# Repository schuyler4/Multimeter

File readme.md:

<h2>Multimeter</h2>
<p>
This is my homebrew multimeter. It differs from standard multimeters in several
respects. 
</p>
<ol>
<li>Only the most used modes are actually included: VDC, Ohms, Capacitance</li>
<li>Powered by a USB cable, no changing batteries.</li> 
<li>Generally a different user interface because of 1 and 2.</li>
</ol>
<p align="center">
</img>
</p>
<h3>Calibration</h3>
<p>
Calibration is relative to my Fluke 101 Multimeter. I know that there
is probably some technical problems with this, as the Fluke 101 does
not have more digits than this meter, nor is it substantially more
 accurate in
voltage mode. However, I don't have a really nice bench top meter, so it 
will have to do. 
</p>
<h3>Specs</h3>
<ul>
<li>Input Resistance: 521kΩ </li>
<li>Range</li>
<ul>
<li>Voltage: +/-60V</li>
<li>Resistance Range 1: 30Ω - 1.2kΩ</li>
<li>Resistance Range 2: 1.2kΩ - 500kΩ</li>
<li>Capacitance: 50nF - 47uF </li>
</ul>
<li>
Relative Accuracy
<ul>
<li> Voltage: 0.5% </li> 
<li> Resistance: 10% </li>
<li> Capacitance: 5% </li>
</ul>
</ul>

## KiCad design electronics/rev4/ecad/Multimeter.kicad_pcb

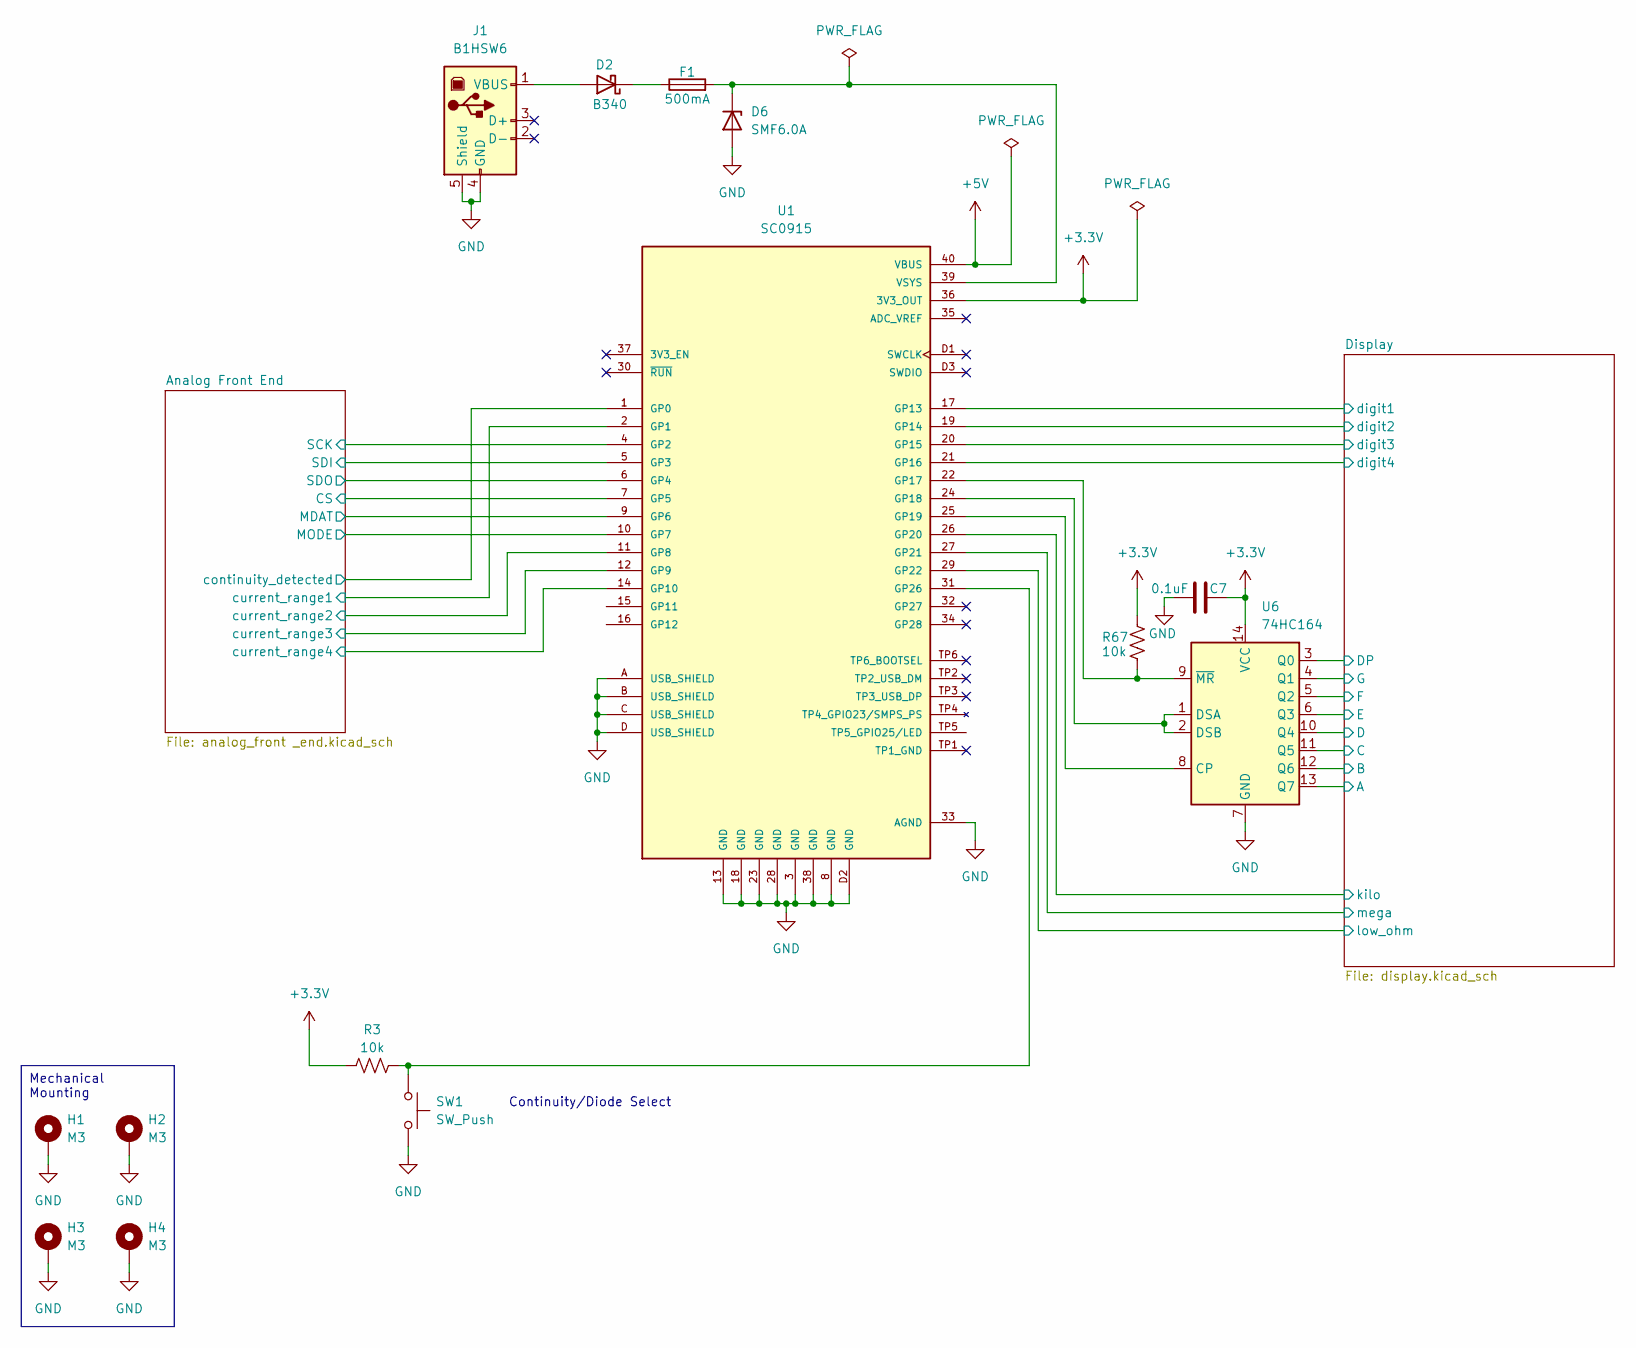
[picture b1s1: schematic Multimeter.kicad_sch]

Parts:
C7: 0.1uF
D2: B340; D_SMB; Part # B340LB-13-F; Digikey Part # B340LB-FDICT-ND
D6: SMF6.0A; D_SOD-123F; Part # SMF6.0A; Digikey Part # F5749CT-ND
F1: 500mA; Fuse_0805_2012Metric; Part # MFU0805FF00500P500; Digikey Part # 749-MFU0805FF00500P500CT-ND
H1, H2, H3, H4: M3; MountingHole_3.2mm_M3_Pad_Via
J1: B1HSW6; USB_B_OST_USB-B1HSxx_Horizontal; Part # USB-B1HSW6; Digikey Part # ED2982-ND
R3: 10k; R_0805_2012Metric; Part # RMCF0805FT10K0; Digikey Part # RMCF0805FT10K0CT-ND
R67: 10k
SW1: SW_Push; SW_PUSH_6mm; Part # TL1105YF160Q; Digikey Part # EG5455-ND
U1: SC0915; MODULE_SC0915; PARTREV 1.9; Digikey Part # 2648-SC0915CT-ND
U6: 74HC164

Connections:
+3.3V: C7.2, R3.1, R67.1, U1.36 (3V3_OUT), U6.14 (VCC); also elsewhere on the board
+5V: U1.40 (VBUS); also elsewhere on the board
/Analog Front End/CS: U1.7 (GP5); also elsewhere on the board
/Analog Front End/MDAT: U1.9 (GP6); also elsewhere on the board
/Analog Front End/MODE: U1.10 (GP7); also elsewhere on the board
/Analog Front End/SCK: U1.4 (GP2); also elsewhere on the board
/Analog Front End/SDI: U1.5 (GP3); also elsewhere on the board
/Analog Front End/SDO: U1.6 (GP4); also elsewhere on the board
/Analog Front End/continuity_detected: U1.1 (GP0); also elsewhere on the board
/Analog Front End/current_range1: U1.2 (GP1); also elsewhere on the board
/Analog Front End/current_range2: U1.11 (GP8); also elsewhere on the board
/Analog Front End/current_range3: U1.12 (GP9); also elsewhere on the board
/Analog Front End/current_range4: U1.14 (GP10); also elsewhere on the board
/Display/A: U1.34 (GP28); also elsewhere on the board
/Display/B: U1.32 (GP27); also elsewhere on the board
/Display/D: U1.29 (GP22); also elsewhere on the board
/Display/DP: U1.24 (GP18), U6.1 (DSA), U6.2 (DSB); also elsewhere on the board
/Display/E: U1.27 (GP21); also elsewhere on the board
/Display/F: U1.26 (GP20); also elsewhere on the board
/Display/G: U1.25 (GP19), U6.8 (CP); also elsewhere on the board
/Display/digit1: U1.17 (GP13); also elsewhere on the board
/Display/digit2: U1.19 (GP14); also elsewhere on the board
/Display/digit3: U1.20 (GP15); also elsewhere on the board
/Display/digit4: U1.21 (GP16); also elsewhere on the board
/Display/kilo: R67.2, U1.22 (GP17), U6.9 (~MR); also elsewhere on the board
/Display/low_ohm: U1.16 (GP12); also elsewhere on the board
/Display/mega: U1.15 (GP11); also elsewhere on the board
GND: C7.1, D6.2 (A), H1.1, H2.1, H3.1, H4.1, J1.4 (GND), J1.5 (Shield), SW1.2, U1.3 (GND), U1.8 (GND), U1.13 (GND), U1.18 (GND), U1.23 (GND), U1.28 (GND), U1.33 (AGND), U1.38 (GND), U1.A (USB_SHIELD), U1.B (USB_SHIELD), U1.C (USB_SHIELD), U1.D (USB_SHIELD), U1.D2 (GND), U6.7 (GND); also elsewhere on the board
unnamed: D2.2 (A), J1.1 (VBUS)
unnamed: D2.1 (K), F1.1
unnamed: D6.1 (K), F1.2, U1.39 (VSYS)

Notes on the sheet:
Mechanical Mounting
Continuity/Diode Select

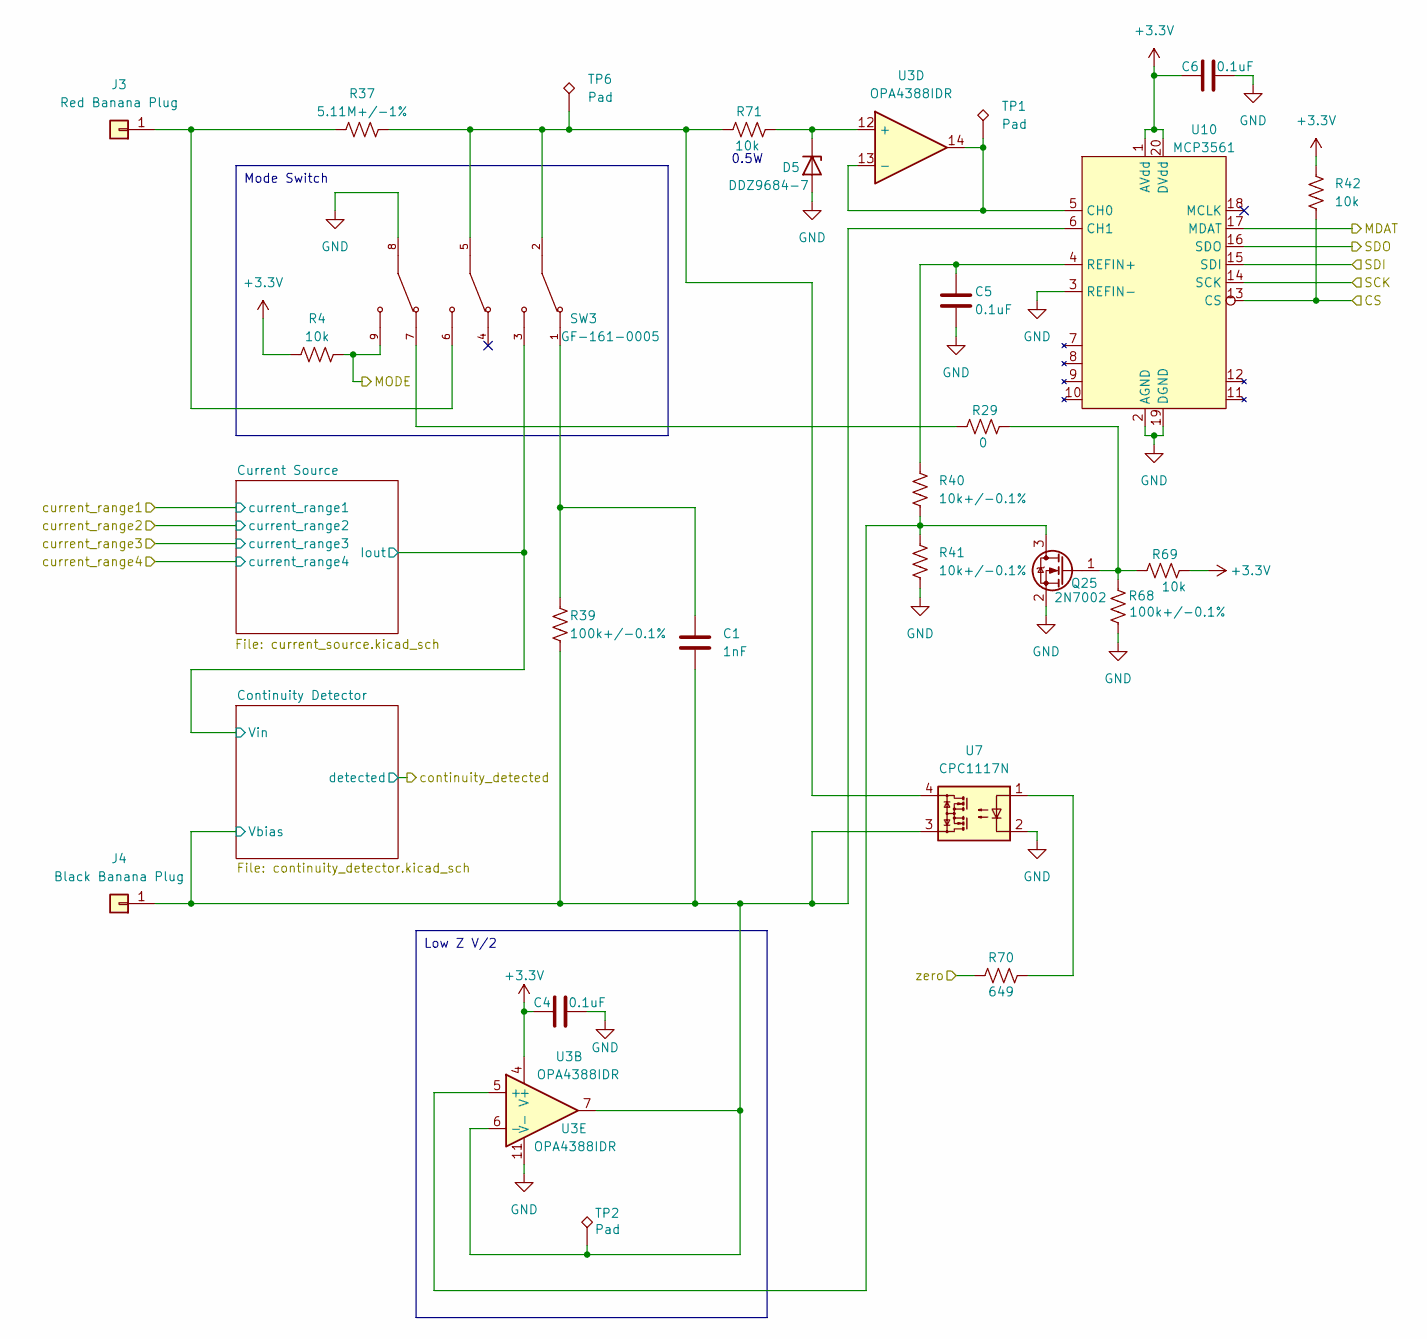
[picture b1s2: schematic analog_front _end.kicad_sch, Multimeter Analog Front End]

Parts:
C1: 1nF; C_0805_2012Metric; Part # CL21B104KBCNNNC; Digikey Part # 1276-1003-1-ND
C4, C5, C6: 0.1uF; C_0805_2012Metric; Part # CL21B104KBCNNNC; Digikey Part # 1276-1003-1-ND
D5: DDZ9684-7; D_SOD-123; Part # DDZ9684-7; Digikey Part # DDZ9684-7DICT-ND
J3: Red Banana Plug; KEYSTONE_575-4; Part # 575-8; Digikey Part # 36-575-8-ND
J4: Black Banana Plug; KEYSTONE_575-4; Part # 575-8; Digikey Part # 36-575-8-ND
Q25: 2N7002; SOT-23; Part # 2N7002; Digikey Part # 2N7002NCT-ND
R4, R42, R69: 10k; R_0805_2012Metric; Part # RMCF0805FT10K0; Digikey Part # RMCF0805FT10K0CT-ND
R29: 0; R_0805_2012Metric; Part # CRCW08050000Z0EA; Digikey Part # 541-0.0ACT-ND
R37: 5.11M+/-1%; R_0805_2012Metric; Part # CRCW08055M11FKEA; Digikey Part # 541-5.11MCCT-ND
R39, R68: 100k+/-0.1%; R_0805_2012Metric; Part # ERA-6AEB104V; Digikey Part # P100KDACT-ND
R40, R41: 10k+/-0.1%; R_0805_2012Metric; Part # ERA-6AEB103V; Digikey Part # P10KDACT-ND
R70: 649
R71: 10k
SW3: GF-161-0005; PARTREV 0; Digikey Part # CWI359-ND
TP1, TP2, TP6: Pad; TestPoint_THTPad_1.5x1.5mm_Drill0.7mm
U3: OPA4388IDR; SOIC-14_3.9x8.7mm_P1.27mm; Part # OPA4388IDR; Digikey Part # 296-53511-1-ND
U7: CPC1117N; SOP-4_3.8x4.1mm_P2.54mm
U10: MCP3561; SSOP-20_4.4x6.5mm_P0.65mm; Part # MCP3561RT-E/ST; Digikey Part # 150-MCP3561RT-E/STCT-ND

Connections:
+3.3V: C4.1, C6.1, R4.1, R42.1, R69.2, U3.4 (V+), U10.1 (AVdd), U10.20 (DVdd); also elsewhere on the board
/Analog Front End/CS: R42.2, U10.13 (CS); also elsewhere on the board
/Analog Front End/Continuity Detector/Vbias: C1.2, J4.1, R39.2, TP2.1, U3.6 (-), U3.7, U7.3, U10.6 (CH1); also elsewhere on the board
/Analog Front End/Current Source/Iout: SW3.3; also elsewhere on the board
/Analog Front End/MDAT: U10.17 (MDAT); also elsewhere on the board
/Analog Front End/MODE: R4.2, SW3.9; also elsewhere on the board
/Analog Front End/SCK: U10.14 (SCK); also elsewhere on the board
/Analog Front End/SDI: U10.15 (SDI); also elsewhere on the board
/Analog Front End/SDO: U10.16 (SDO); also elsewhere on the board
GND: C4.2, C5.2, C6.2, D5.2 (A), Q25.2 (S), R41.2, R68.1, SW3.8, U3.11 (V-), U7.2, U10.2 (AGND), U10.3 (REFIN-), U10.19 (DGND); also elsewhere on the board
unnamed: C1.1, R39.1, SW3.1
unnamed: Q25.3 (D), R40.2, R41.1, U3.5 (+)
unnamed: Q25.1 (G), R29.2, R68.2, R69.1
unnamed: R29.1, SW3.7
unnamed: R70.2, U7.1
unnamed: TP1.1, U3.13 (-), U3.14, U10.5 (CH0)
unnamed: C5.1, R40.1, U10.4 (REFIN+)

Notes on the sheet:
Low Z V/2
Mode Switch
0.5W

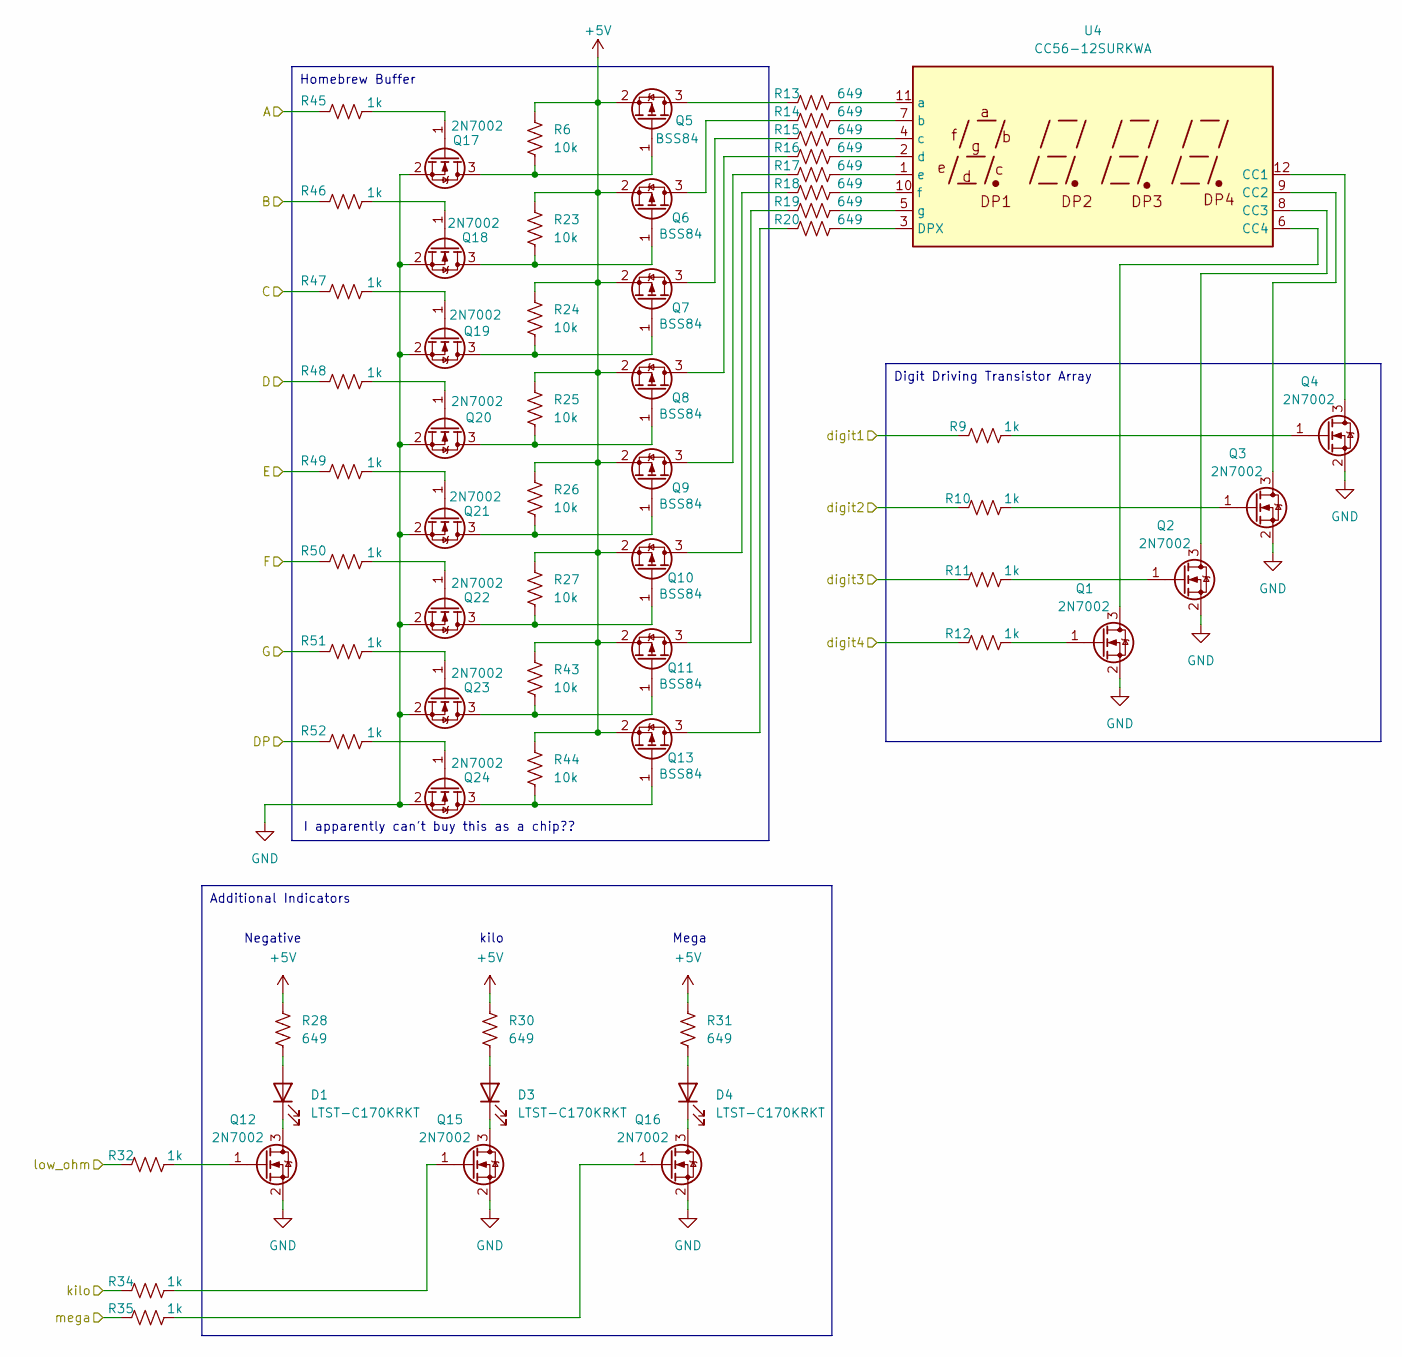
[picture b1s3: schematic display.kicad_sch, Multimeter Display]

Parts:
D1, D3, D4: LTST-C170KRKT; LED_0805_2012Metric; Part # LTST-C170KRKT; Digikey Part # 160-1415-1-ND
Q1, Q2, Q3, Q4, Q12, Q15, Q16, Q17, Q18, Q19, Q20, Q21, Q22, Q23, Q24: 2N7002; SOT-23; Part # 2N7002; Digikey Part # 2N7002NCT-ND
Q5, Q6, Q7, Q8, Q9, Q10, Q11, Q13: BSS84; SOT-23; Part # BSS84; Digikey Part # BSS84CT-ND
R6, R23, R24, R25, R26, R27, R43, R44: 10k; R_0805_2012Metric; Part # RMCF0805FT10K0; Digikey Part # RMCF0805FT10K0CT-ND
R9, R10, R11, R12, R32, R34, R35, R45, R46, R47, R48, R49, R50, R51, R52: 1k; R_0805_2012Metric; Part # RMCF0805FT1K00; Digikey Part # RMCF0805FT1K00CT-ND
R13, R14, R15, R16, R17, R18, R19, R20, R28, R30, R31: 649; R_0805_2012Metric; Part # RMCF0805FT649R; Digikey Part # RMCF0805FT649RCT-ND
U4: CC56-12SURKWA; CA56-12SURKWA; Part # CC56-12SURKWA; Digikey Part # 754-CC56-12SURKWA-ND

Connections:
+5V: Q5.2 (S), Q6.2 (S), Q7.2 (S), Q8.2 (S), Q9.2 (S), Q10.2 (S), Q11.2 (S), Q13.2 (S), R6.1, R23.1, R24.1, R25.1, R26.1, R27.1, R28.1, R30.1, R31.1, R43.1, R44.1; also elsewhere on the board
/Display/A: R45.1; also elsewhere on the board
/Display/B: R46.1; also elsewhere on the board
/Display/D: R48.1; also elsewhere on the board
/Display/DP: R52.1; also elsewhere on the board
/Display/E: R49.1; also elsewhere on the board
/Display/F: R50.1; also elsewhere on the board
/Display/G: R51.1; also elsewhere on the board
/Display/digit1: R9.1; also elsewhere on the board
/Display/digit2: R10.1; also elsewhere on the board
/Display/digit3: R11.1; also elsewhere on the board
/Display/digit4: R12.1; also elsewhere on the board
/Display/kilo: R34.1; also elsewhere on the board
/Display/low_ohm: R32.1; also elsewhere on the board
/Display/mega: R35.1; also elsewhere on the board
GND: Q1.2 (S), Q2.2 (S), Q3.2 (S), Q4.2 (S), Q12.2 (S), Q15.2 (S), Q16.2 (S), Q17.2 (S), Q18.2 (S), Q19.2 (S), Q20.2 (S), Q21.2 (S), Q22.2 (S), Q23.2 (S), Q24.2 (S); also elsewhere on the board
unnamed: D1.2 (A), R28.2
unnamed: D1.1 (K), Q12.3 (D)
unnamed: D3.2 (A), R30.2
unnamed: D3.1 (K), Q15.3 (D)
unnamed: D4.2 (A), R31.2
unnamed: D4.1 (K), Q16.3 (D)
unnamed: Q1.3 (D), U4.6 (CC4)
unnamed: Q1.1 (G), R12.2
unnamed: Q2.3 (D), U4.8 (CC3)
unnamed: Q2.1 (G), R11.2
unnamed: Q3.3 (D), U4.9 (CC2)
unnamed: Q3.1 (G), R10.2
unnamed: Q4.3 (D), U4.12 (CC1)
unnamed: Q4.1 (G), R9.2
unnamed: Q5.3 (D), R13.1
unnamed: Q6.3 (D), R14.1
unnamed: Q7.3 (D), R15.1
unnamed: Q8.3 (D), R16.1
unnamed: Q9.3 (D), R17.1
unnamed: Q10.3 (D), R18.1
unnamed: Q10.1 (G), Q22.3 (D), R27.2
unnamed: Q11.3 (D), R19.1
unnamed: Q11.1 (G), Q23.3 (D), R43.2
unnamed: Q12.1 (G), R32.2
unnamed: Q13.3 (D), R20.1
unnamed: Q13.1 (G), Q24.3 (D), R44.2
unnamed: Q15.1 (G), R34.2
unnamed: Q16.1 (G), R35.2
unnamed: Q5.1 (G), Q17.3 (D), R6.2
unnamed: Q17.1 (G), R45.2
unnamed: Q6.1 (G), Q18.3 (D), R23.2
unnamed: Q18.1 (G), R46.2
unnamed: Q7.1 (G), Q19.3 (D), R24.2
unnamed: Q19.1 (G), R47.2
unnamed: Q8.1 (G), Q20.3 (D), R25.2
unnamed: Q20.1 (G), R48.2
unnamed: Q9.1 (G), Q21.3 (D), R26.2
unnamed: Q21.1 (G), R49.2
unnamed: Q22.1 (G), R50.2
unnamed: Q23.1 (G), R51.2
unnamed: Q24.1 (G), R52.2
unnamed: R20.2, U4.3 (DPX)
unnamed: R13.2, U4.11 (a)
unnamed: R14.2, U4.7 (b)
unnamed: R15.2, U4.4 (c)
unnamed: R16.2, U4.2 (d)
unnamed: R17.2, U4.1 (e)
unnamed: R18.2, U4.10 (f)
unnamed: R19.2, U4.5 (g)

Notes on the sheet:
Digit Driving Transistor Array
Homebrew Buffer
Additional Indicators
kilo
I apparently can't buy this as a chip??
Mega
Negative

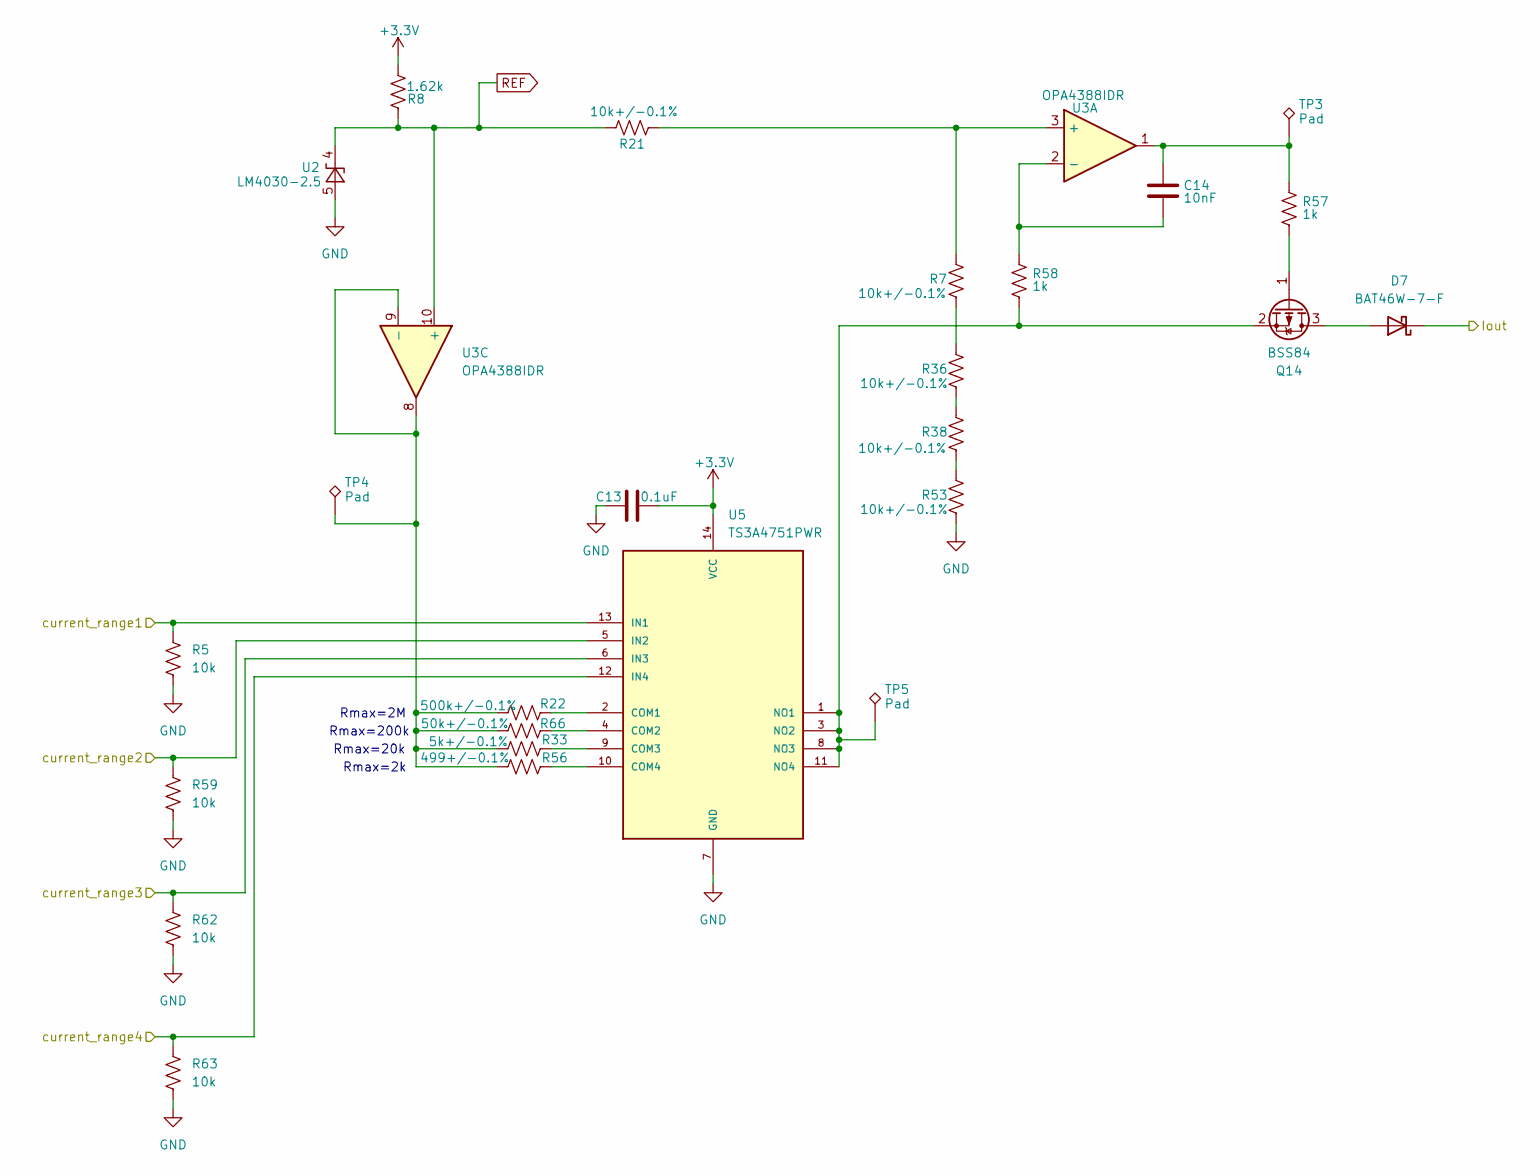
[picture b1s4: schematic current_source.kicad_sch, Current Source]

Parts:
C13: 0.1uF; C_0805_2012Metric; Part # CL21B104KBCNNNC; Digikey Part # 1276-1003-1-ND
C14: 10nF; C_0805_2012Metric; Part # C0805C103K5RACTU; Digikey Part # 399-C0805C103K5RACTUCT-ND
D7: BAT46W-7-F; D_SOD-123; Part # BAT46W-7-F; Digikey Part # BAT46W-7FDICT-ND
Q14: BSS84; SOT-23; Part # BSS84; Digikey Part # BSS84CT-ND
R5, R59, R62, R63: 10k; R_0805_2012Metric; Part # RMCF0805FT10K0; Digikey Part # RMCF0805FT10K0CT-ND
R7, R21, R36, R38, R53: 10k+/-0.1%; R_0805_2012Metric; Part # ERA-6AEB103V; Digikey Part # P10KDACT-ND
R8: 1.62k; R_0805_2012Metric; Part # RMCF0805FT1K62; Digikey Part # RMCF0805FT1K62CT-ND
R22: 500k+/-0.1%; R_0805_2012Metric; Part # RNCF0805BTE500K; Digikey Part # 738-RNCF0805BTE500KCT-ND
R33: 5k+/-0.1%; R_0805_2012Metric; Part # PNM0805E5001BST5; Digikey Part # PNM0805-5.0KBCT-ND
R56: 499+/-0.1%; R_0805_2012Metric; Part # ERA-6AEB4990V; Digikey Part # P499DACT-ND
R57, R58: 1k; R_0805_2012Metric; Part # RMCF0805FT1K00; Digikey Part # RMCF0805FT1K00CT-ND
R66: 50k+/-0.1%; R_0805_2012Metric; Part # MCU08050D5002BP100; Digikey Part # 749-MCU08050D5002BP100CT-ND
TP3, TP4, TP5: Pad; TestPoint_THTPad_1.5x1.5mm_Drill0.7mm
U2: LM4030-2.5; SOT-23-5; Part # LM4030CMF-2.5/NOPB; Digikey Part # LM4030CMF-2.5/NOPBCT-ND
U3: OPA4388IDR; SOIC-14_3.9x8.7mm_P1.27mm; Part # OPA4388IDR; Digikey Part # 296-53511-1-ND
U5: TS3A4751PWR; TSSOP-14_4.4x5mm_P0.65mm; PARTREV F; Digikey Part # 296-20700-1-ND

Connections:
+3.3V: C13.2, R8.1, U5.14 (VCC); also elsewhere on the board
/Analog Front End/Current Source/Iout: D7.1 (K); also elsewhere on the board
/Analog Front End/current_range1: R5.1, U5.13 (IN1); also elsewhere on the board
/Analog Front End/current_range2: R59.1, U5.5 (IN2); also elsewhere on the board
/Analog Front End/current_range3: R62.1, U5.6 (IN3); also elsewhere on the board
/Analog Front End/current_range4: R63.1, U5.12 (IN4); also elsewhere on the board
GND: C13.1, R5.2, R53.2, R59.2, R62.2, R63.2, U2.5 (A), U5.7 (GND); also elsewhere on the board
unnamed: C14.1, R57.1, TP3.1, U3.1
unnamed: D7.2 (A), Q14.3 (D)
unnamed: Q14.1 (G), R57.2
unnamed: Q14.2 (S), R58.2, TP5.1, U5.1 (NO1), U5.3 (NO2), U5.8 (NO3), U5.11 (NO4)
unnamed: R7.2, R36.1
unnamed: R36.2, R38.1
unnamed: R38.2, R53.1
unnamed: R7.1, R21.2, U3.3 (+)
unnamed: C14.2, R58.1, U3.2 (-)
unnamed: R22.1, R33.1, R56.1, R66.1, TP4.1, U3.8, U3.9 (-)
unnamed: R22.2, U5.2 (COM1)
unnamed: R66.2, U5.4 (COM2)
unnamed: R33.2, U5.9 (COM3)
unnamed: R56.2, U5.10 (COM4)
REF: R8.2, R21.1, U2.4 (K), U3.10 (+); also elsewhere on the board

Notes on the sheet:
Rmax=2M
Rmax=2k
Rmax=20k
Rmax=200k

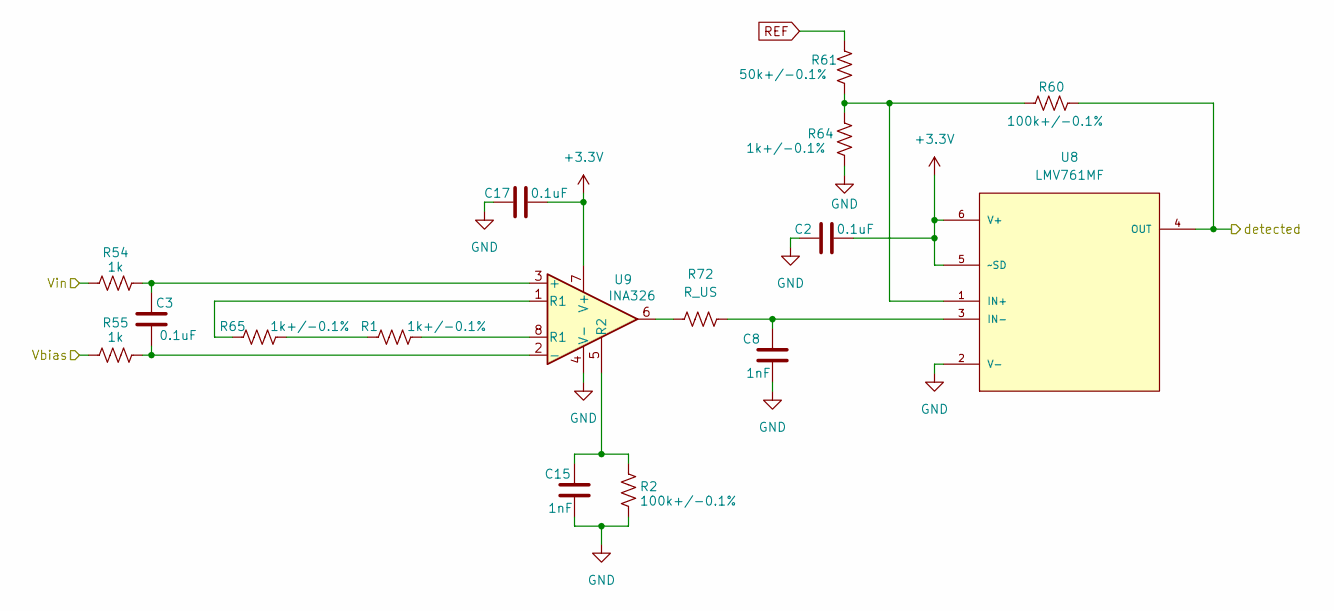
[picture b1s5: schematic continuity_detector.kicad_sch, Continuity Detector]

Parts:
C2, C3, C17: 0.1uF; C_0805_2012Metric; Part # CL21B104KBCNNNC; Digikey Part # 1276-1003-1-ND
C8, C15: 1nF; C_0805_2012Metric; Part # C0805C102J5GACTU; Digikey Part # 399-C0805C102J5GACTUCT-ND
R1, R64, R65: 1k+/-0.1%; R_0805_2012Metric; Part # CRCW08051K00FKEA; Digikey Part # 541-1.00KCCT-ND
R2, R60: 100k+/-0.1%; R_0805_2012Metric; Part # ERA-6AEB104V; Digikey Part # P100KDACT-ND
R54, R55: 1k; R_0805_2012Metric; Part # RMCF0805FT1K00; Digikey Part # RMCF0805FT1K00CT-ND
R61: 50k+/-0.1%; R_0805_2012Metric; Part # MCU08050D5002BP100; Digikey Part # 749-MCU08050D5002BP100CT-ND
R72: R_US
U8: LMV761MF; SOT-23-6; MPN LMV761MF; Digikey Part # LMV761MFCT-ND
U9: INA326; MSOP-8_3x3mm_P0.65mm; Part # INA326EA/2K5; Digikey Part # INA326EA/2K5CT-ND

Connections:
+3.3V: C2.2, C17.2, U8.5 (~SD), U8.6 (V+), U9.7 (V+); also elsewhere on the board
/Analog Front End/Continuity Detector/Vbias: R55.1; also elsewhere on the board
/Analog Front End/continuity_detected: R60.2, U8.4 (OUT); also elsewhere on the board
GND: C2.1, C8.2, C15.2, C17.1, R2.2, R64.2, U8.2 (V-), U9.4 (V-); also elsewhere on the board
unnamed: R1.1, R65.2
unnamed: R1.2, U9.8 (R1)
unnamed: R65.1, U9.1 (R1)
unnamed: R60.1, R61.2, R64.1, U8.1 (IN+)
unnamed: C8.1, R72.1, R72.2, U8.3 (IN-), U9.6
unnamed: C3.1, R54.2, U9.3 (+)
unnamed: C3.2, R55.2, U9.2 (-)
unnamed: C15.1, R2.1, U9.5 (R2)
REF: R61.1; also elsewhere on the board

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
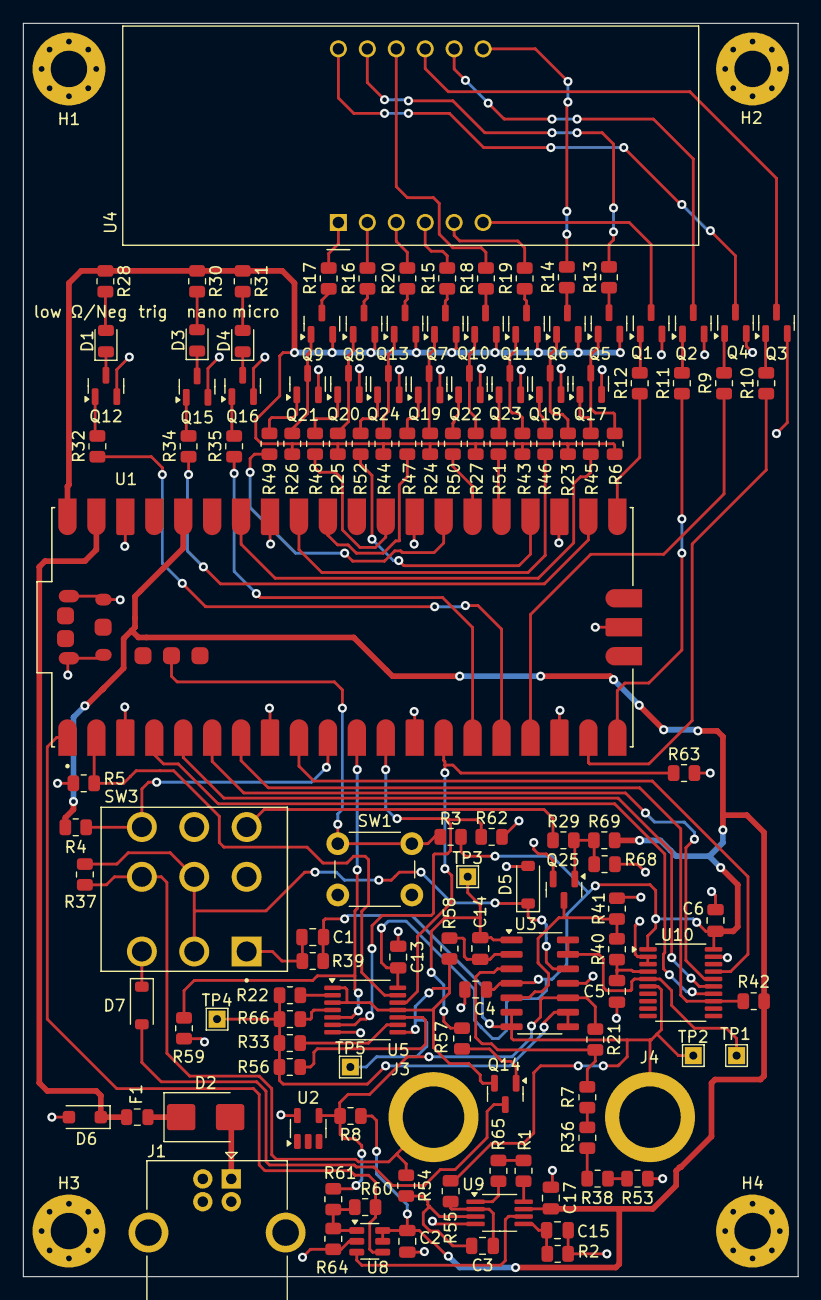
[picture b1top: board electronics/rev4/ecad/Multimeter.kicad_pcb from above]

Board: 2 copper layers, 68.0 x 110.0 mm, 133 parts (0 on the bottom side), 115 nets.

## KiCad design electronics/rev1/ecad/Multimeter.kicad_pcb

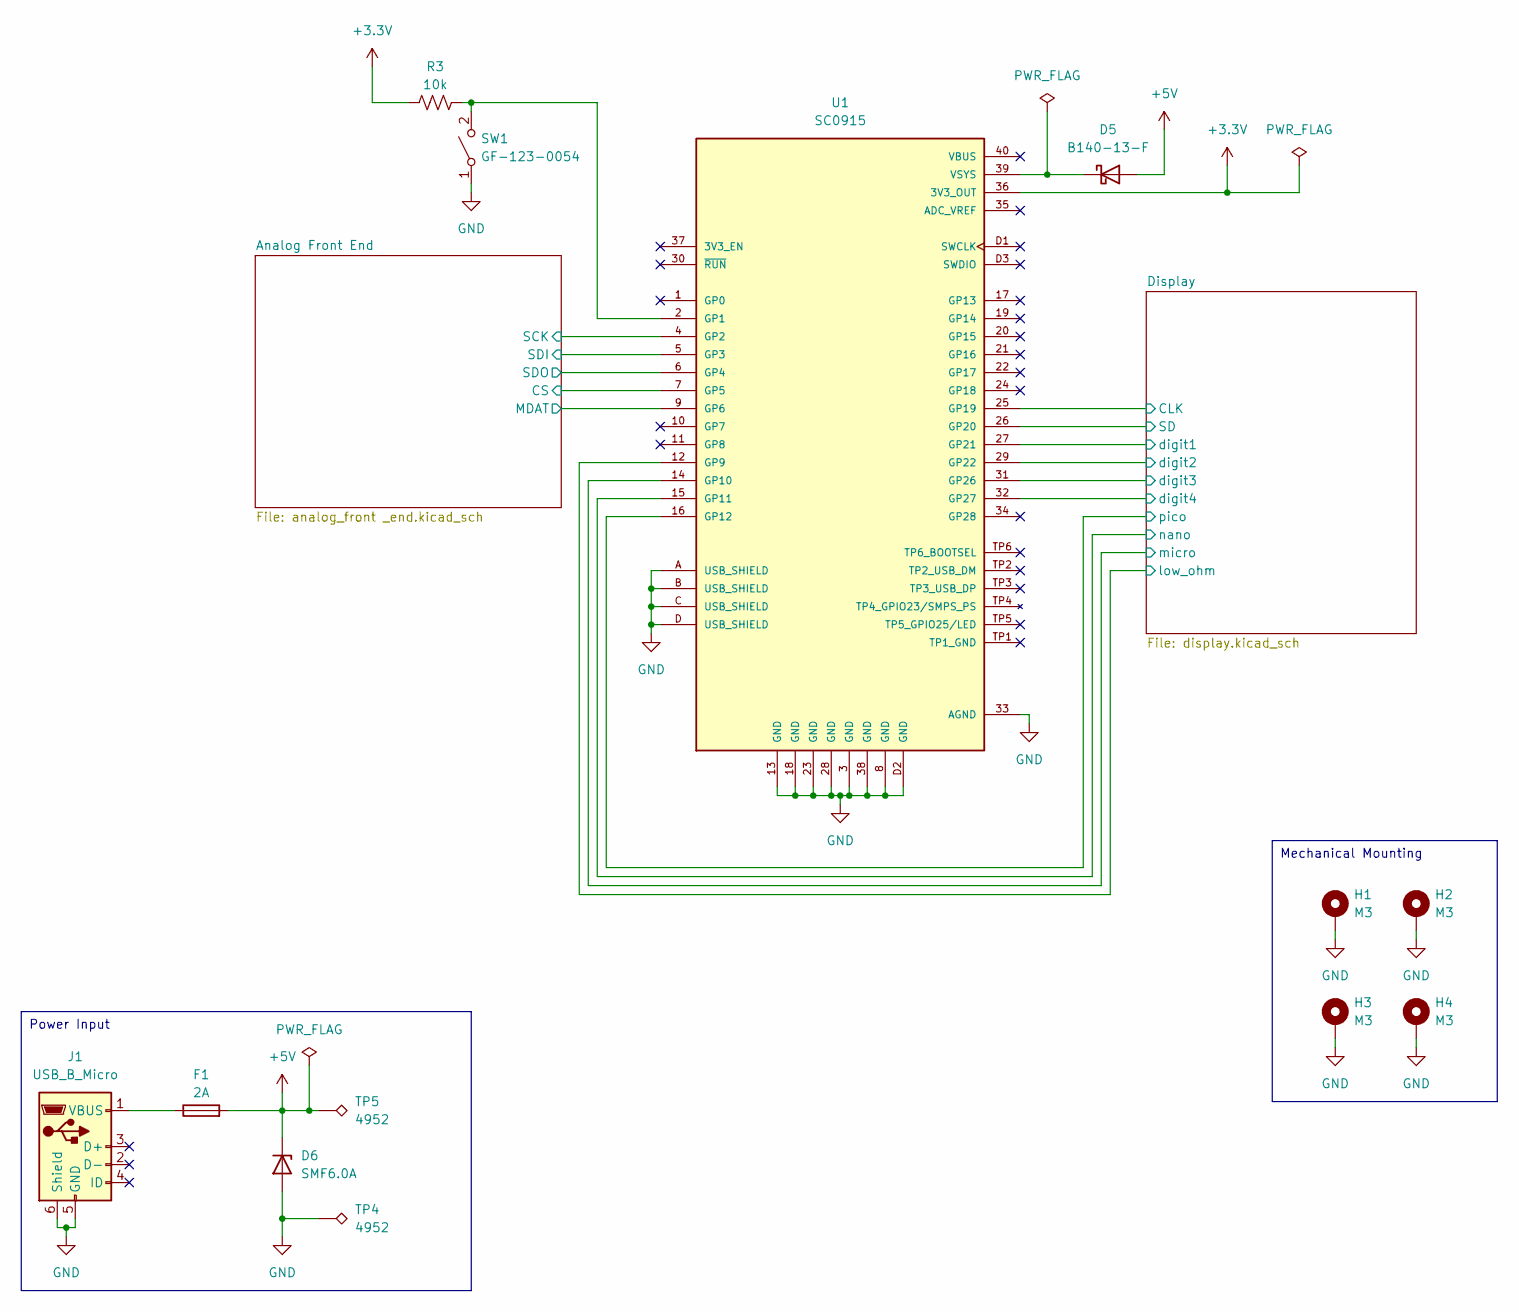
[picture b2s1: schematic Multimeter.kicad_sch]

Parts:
D5: B140-13-F; D_0805_2012Metric; Part # B140-13-F; Digikey Part # B140-FDICT-ND
D6: SMF6.0A; D_SOD-123F; Part # SMF6.0A; Digikey Part # F5749CT-ND
F1: 2A; D_0805_2012Metric; Part # FCC20202AATP; Digikey Part # 2315-FCC20202AATPCT-ND
H1, H2, H3, H4: M3; MountingHole_2.7mm_Pad_Via
J1: USB_B_Micro; USB_Micro-AB_Molex_47590-0001; Part # 0475900001; Digikey Part # WM17144CT-ND
R3: 10k; C_0805_2012Metric_Pad1.18x1.45mm_HandSolder; Part # RMCF0805FT10K0; Digikey Part # RMCF0805FT10K0CT-ND
SW1: GF-123-0054; SW_GF-123-0054; Part # GF-123-0054; Digikey Part # CWI333-ND
TP4, TP5: 4952; TestPoint_THTPad_1.5x1.5mm_Drill0.7mm; Part # 4952; Digikey Part # 36-4952-ND
U1: SC0915; MODULE_SC0915; Part # SC0915; Digikey Part # 2648-SC0915CT-ND

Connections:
+3.3V: R3.1, U1.36 (3V3_OUT); also elsewhere on the board
+5V: D5.2 (A), D6.1 (K), F1.2, TP5.1; also elsewhere on the board
/Analog Front End/CS: U1.7 (GP5); also elsewhere on the board
/Analog Front End/MDAT: U1.9 (GP6); also elsewhere on the board
/Analog Front End/SCK: U1.4 (GP2); also elsewhere on the board
/Analog Front End/SDI: U1.5 (GP3); also elsewhere on the board
/Analog Front End/SDO: U1.6 (GP4); also elsewhere on the board
/Display/CLK: U1.25 (GP19); also elsewhere on the board
/Display/SD: U1.26 (GP20); also elsewhere on the board
/Display/digit1: U1.27 (GP21); also elsewhere on the board
/Display/digit2: U1.29 (GP22); also elsewhere on the board
/Display/digit3: U1.31 (GP26); also elsewhere on the board
/Display/digit4: U1.32 (GP27); also elsewhere on the board
/Display/low_ohm: U1.12 (GP9); also elsewhere on the board
/Display/micro: U1.14 (GP10); also elsewhere on the board
/Display/nano: U1.15 (GP11); also elsewhere on the board
/Display/pico: U1.16 (GP12); also elsewhere on the board
GND: D6.2 (A), H1.1, H2.1, H3.1, H4.1, J1.5 (GND), J1.6 (Shield), SW1.1 (A), TP4.1, U1.3 (GND), U1.8 (GND), U1.13 (GND), U1.18 (GND), U1.23 (GND), U1.28 (GND), U1.33 (AGND), U1.38 (GND), U1.A (USB_SHIELD), U1.B (USB_SHIELD), U1.C (USB_SHIELD), U1.D (USB_SHIELD), U1.D2 (GND); also elsewhere on the board
unnamed: D5.1 (K), U1.39 (VSYS)
unnamed: F1.1, J1.1 (VBUS)
unnamed: R3.2, SW1.2 (B), U1.2 (GP1)

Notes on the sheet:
Power Input
Mechanical Mounting
